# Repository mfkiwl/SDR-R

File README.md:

# SDR-R
Software Defined Radio Receiver(SDR-R) for UMBC Computer Engineering Capstone FA18-SP19

The purpose of this repository will be for tracking of source code changes/additions and team collaboration for the development of this SDR-R. This will facilitate in project organization and documentation.

__Note__: [The home for this repository can be found here](https://github.com/carrera1/SDR-R)

## Directories

__fpga-src/__

Source code for any/all HDL written for the FPGA.

__hw__

Directory for all files related to hardware

__sw-src/__

Source code for any/all C/C++, Matlab/Simulink, or Python code generated.

__vm-info/__

Relevant documentation pertaining to the software development environment is kept here (i.e. list of needed packages). 
This directory also includes an important readme file for setting up important dependencies on your machine. The code 
provided in **sw-src** should function on unix/linux style machines (to include macOS), as long as the relevant dependencies 
are available (mainly pthreads, libftdi, and libusb).

## Set up and Installation

__FPGA__

For any future capstone groups looking back on this, we apologize that the **fpga-src** directory is one of the less organized 
of the bunch. Of the blocks utilized, all but the Xilinx IP cores are here in this repository. These IP cores include a 
clock generator (which should be simple to set up) and a FIFO for interfacing the Rader ("link") block with the FSM 
handling the interfacing with the FTDI chip. The FPGA->FTDI FIFO should have a write width of 16 and a read width of 8. 
The FTDI->FPGA FIFO is written by use for handling the messages sent from the host computer to the FPGA. It is **not** meant 
for interfacing with the Rader block.

__Software__

Instructions for setting up your development environment can be found in **vm-info**. Please, follow the instructions there 
for setting up many of the minor dependencies needed for this project before continuing here.

This project has 2 major dependencies (each with their own sub-dependencies) that are critical for functionality:

* GNU Radio
  - Instructions for setting up found in **vm-info** directory
* libftdi
  - Open source library for writing code the interact with the FT232H bridge we're utilizing
  - Requires **libusb 1.0**, please install this on your system prior to installing libftdi
  - Requires **libconfuse**, please install this on your system prior to installing libftdi

### Installing libftdi

```bash
git://developer.intra2net.com/libftdi
cd libftdi
# READ THE READMEs IN YOUR FAVORITE TEXT EDITOR
```

The libftdi developers included *verbose* instructions within the repository you just cloned. Please read them thoroughly. 
They also include numerous examples demonstrating the functionality of the library, where this project drew heavily from the **stream-test.c**.

The libftdi developers also have their documentation available online which you may find necessary to understand how each 
function works and what their return values may be. [To save you time, you may find it here!](https://www.intra2net.com/en/developer/libftdi/documentation/group__libftdi.html)

Once both GNU Radio and libftdi are installed, software side set up is done. If the FPGA is properly set up, then you're good 
to compile and run the code found in **sw-src**.

## Acknowledgements

This project wouldn't be what it is without the inspiration drawn from the following:
* [This blog post](https://digibird1.wordpress.com/adc-readout-and-usb2-0-data-transfer-with-an-fpga/) for inspiring us to try out an FTDI chip instead of terrible terrible UART.
* [This github repo](https://github.com/RandomReaper/pim-vhdl) for providing an open source FSM for interfacing with the FT232H. Many thanks to [Mssr. Marc Pignat](https://github.com/RandomReaper)!

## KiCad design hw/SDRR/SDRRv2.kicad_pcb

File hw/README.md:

# Hardware Directory

All relevant files or documentation related to hardware should be kept here.

Please keep arrangement neat and logical for the sake of other people's sanity

When convenient or necessary, document this readme to explain the organization of this subdirectory

See other readmes as an example for consistant formatting

## Directories

__SDRR__

KiCad design files

__Chips__

Downloaded library files for IC's in schematic

__Datasheets__

Data sheets for the IC's

__FAB__

Output files from PCB design, for fabrication

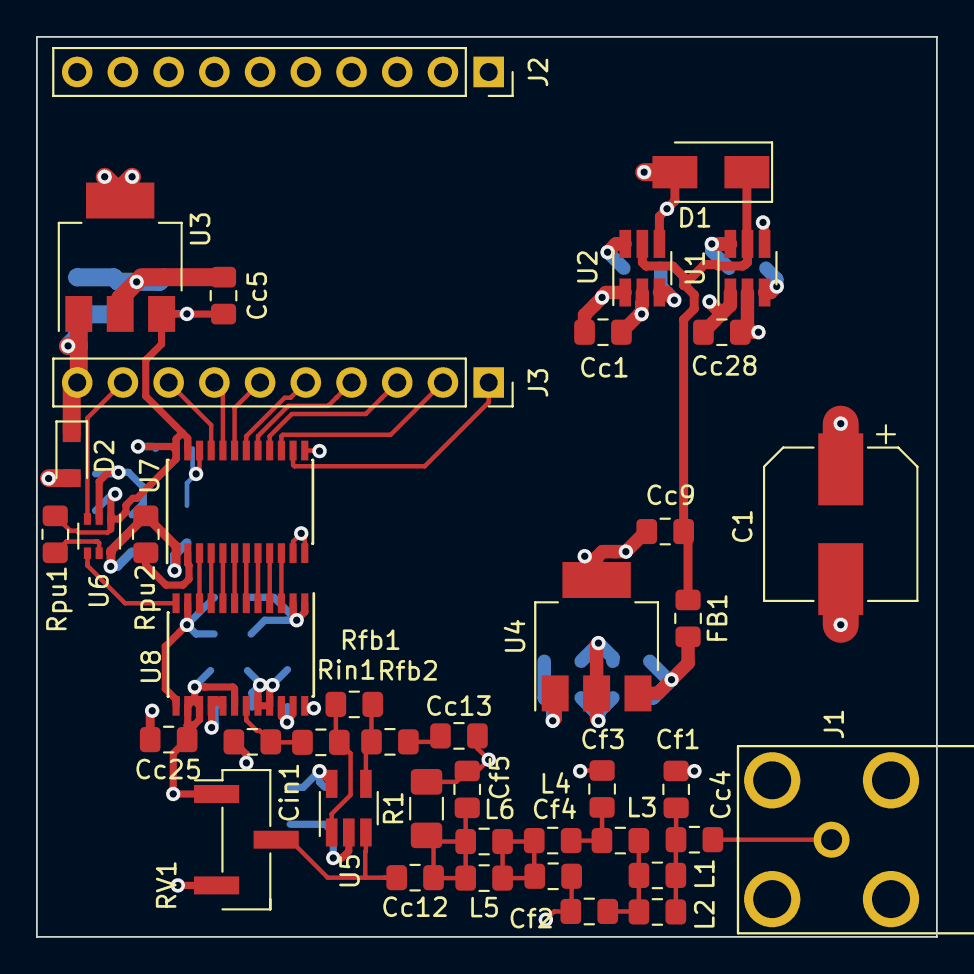
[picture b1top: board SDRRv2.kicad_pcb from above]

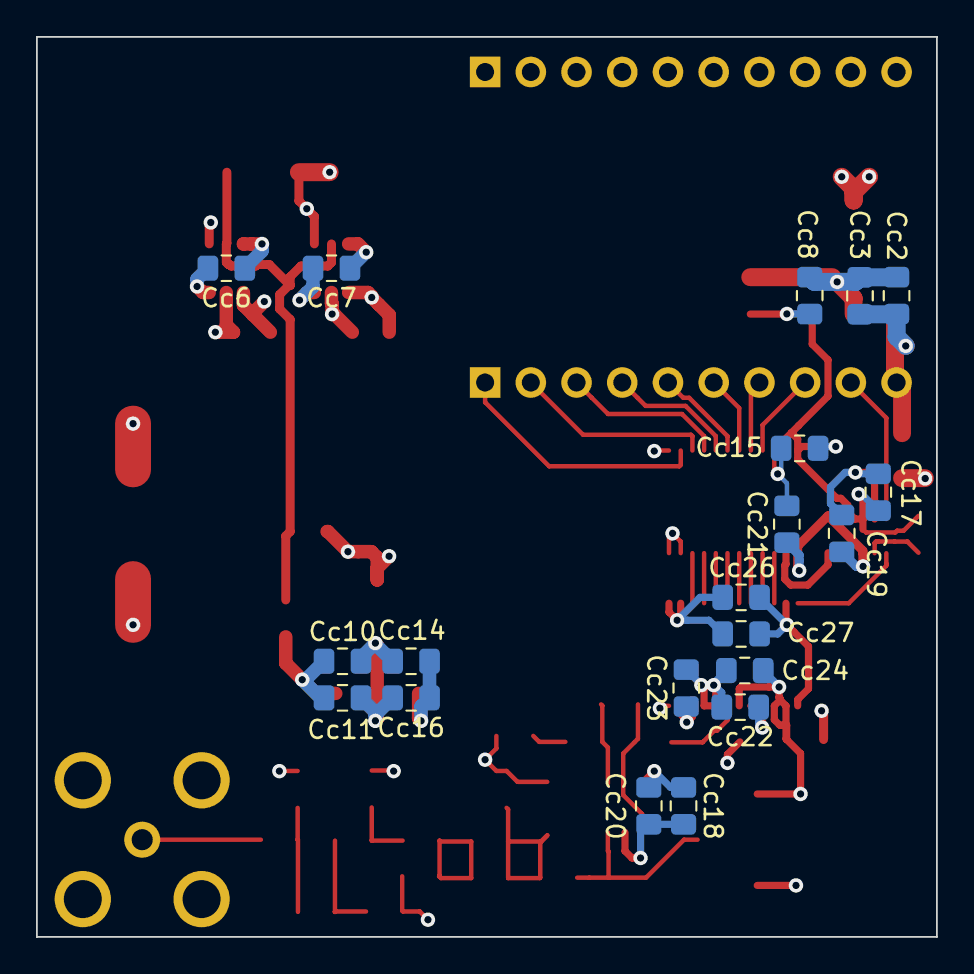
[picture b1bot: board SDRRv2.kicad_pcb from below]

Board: 4 copper layers, 50.0 x 50.0 mm, 62 parts (20 on the bottom side), 43 nets.

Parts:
C1: 47u; CP_Elec_8x6.2
Cc1, Cc3, Cc4, Cc5, Cc6, Cc7, Cc9, Cc10, Cc12, Cc13, Cc14, Cc15, Cc17, Cc18, Cc19, Cc21, Cc25, Cc27, Cc28: 10u; C_0805_2012Metric_Pad1.15x1.40mm_HandSolder
Cc2, Cc8, Cc11, Cc16, Cc20, Cc24, Cc26: 0.1u; C_0805_2012Metric_Pad1.15x1.40mm_HandSolder
Cc22, Cc23: 10uF; C_0805_2012Metric_Pad1.15x1.40mm_HandSolder
Cf1, Cf5: 150pF; C_0805_2012Metric_Pad1.15x1.40mm_HandSolder
Cf2, Cf4: 680pF; C_0805_2012Metric_Pad1.15x1.40mm_HandSolder
Cf3: 910pF; C_0805_2012Metric_Pad1.15x1.40mm_HandSolder
Cin1: 62pF; C_0805_2012Metric_Pad1.15x1.40mm_HandSolder
D1: B120-E3; D_SMA
D2: D_TVS; D_SOD-323_HandSoldering
FB1: L_Core_Ferrite; L_0805_2012Metric_Pad1.15x1.40mm_HandSolder
J1: Conn_Coaxial; TE_5-1634513-1
J2, J3: Conn_01x10_Female; PinSocket_1x10_P2.54mm_Vertical
L1, L2, L3, L4, L5, L6: 2.2u; L_0805_2012Metric_Pad1.15x1.40mm_HandSolder
R1: 50; R_1206_3216Metric_Pad1.42x1.75mm_HandSolder
RV1: R_POT; PinHeader_1x03_P2.54mm_Vertical_SMD_Pin1Left
Rfb1, Rfb2: 270; R_0805_2012Metric_Pad1.15x1.40mm_HandSolder
Rin1: 110; R_0805_2012Metric_Pad1.15x1.40mm_HandSolder
Rpu1, Rpu2: 10k; R_0805_2012Metric_Pad1.15x1.40mm_HandSolder
U1, U2: LM2766M6X_NOPB; SOT-23-6_Handsoldering
U3: UA78M33CDCY; SOT-223-3_TabPin2
U4: UA78M05IDCY; SOT-223-3_TabPin2
U5: OPA354AIDBVR; SOT-23-5_HandSoldering
U6: SN74LVC1T45DCK; SOT-363_SC-70-6
U7: SN74LVC8T245PWR; TSSOP-24_4.4x7.8mm_P0.65mm
U8: ADC1173; TSSOP-24_4.4x7.8mm_P0.65mm

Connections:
+3V3: Cc5.1, Cc8.1, Cc15.2, Cc17.1, Rpu1.1, U3.3, U6.1, U7.23, U7.24
+5V: C1.1, Cc1.1, Cc2.1, Cc3.1, Cc19.1, Cc21.1, Cc26.1, Cc27.1, Cc28.1, D1.2, D2.1, J3.10, Rpu2.1, U1.1, U1.4, U2.1, U2.4, U3.1, U6.6, U7.1, U8.11, U8.13
+5VA: Cc14.1, Cc16.1, Cc18.1, Cc20.1, Cc24.2, Cc25.2, RV1.1, U4.1, U5.5, U8.14, U8.15, U8.18
GNDREF: C1.2, Cc1.2, Cc2.2, Cc3.2, Cc5.2, Cc8.2, Cc9.2, Cc10.2, Cc11.2, Cc13.2, Cc14.2, Cc15.1, Cc16.2, Cc17.2, Cc18.2, Cc19.2, Cc20.2, Cc21.2, Cc22.2, Cc23.2, Cc24.1, Cc25.1, Cc26.2, Cc27.2, Cc28.2, Cf1.2, Cf2.2, Cf3.2, Cf4.2, Cf5.2, Cin1.2, D2.2, J1.2, J2.10, R1.2, RV1.3, U1.2, U2.2, U3.2, U4.2, U5.2, U6.2, U7.11, U7.12, U7.13, U7.22, U8.1, U8.2, U8.20, U8.21, U8.24
unnamed: Cc4.1, J1.1
unnamed: Cc4.2, Cf1.1, L1.1, L2.1
unnamed: Cc6.1, U1.6
unnamed: Cc6.2, U1.3
unnamed: Cc7.1, U2.6
unnamed: Cc7.2, U2.3
unnamed: Cc9.1, D1.1, FB1.1, U1.5, U2.5
unnamed: Cc10.1, Cc11.1, FB1.2, U4.3
unnamed: Cc12.1, Cf5.1, L5.2, L6.2, R1.1
unnamed: Cc12.2, RV1.2, U5.3
unnamed: Cc13.1, Rfb2.2
unnamed: Cc22.1, U8.16, U8.17
unnamed: Cc23.1, U8.22, U8.23
unnamed: Cf2.1, L1.2, L2.2, L3.1
unnamed: Cf3.1, L3.2, L4.1
unnamed: Cf4.1, L4.2, L5.1, L6.1
unnamed: Cin1.1, Rin1.2, U8.19
unnamed: J3.1, U7.14
unnamed: J3.2, U7.15
unnamed: J3.3, U7.16
unnamed: J3.4, U7.17
unnamed: J3.5, U7.18
unnamed: J3.6, U7.19
unnamed: J3.7, U7.20
unnamed: J3.8, U7.21
unnamed: J3.9, U6.3
unnamed: Rfb1.1, Rin1.1, U5.1
unnamed: Rfb1.2, Rfb2.1, U5.4
unnamed: Rpu1.2, U6.5
unnamed: Rpu2.2, U7.2
unnamed: U6.4, U8.12
unnamed: U7.3, U8.10
unnamed: U7.4, U8.9
unnamed: U7.5, U8.8
unnamed: U7.6, U8.7
unnamed: U7.7, U8.6
unnamed: U7.8, U8.5
unnamed: U7.9, U8.4
unnamed: U7.10, U8.3

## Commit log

2018-11-04 Initial commit. Updated readmes.
2018-11-07 Testing file. Remove later
2018-11-07 removing testfile
2018-11-07 Added set up instructions for VM
2018-11-07 Added recommended package to list
2018-11-07 Proof reading/editing
2018-11-07 Proof reading
2018-11-09 Amended sections that were optional
2018-11-14 Added constraints file for CMOD-A7
2018-11-25 Added directory for files related to hardware
2018-11-25 Added entry for HW directory
2018-11-25 minimal edit
2018-11-25 Silly typo
2018-11-25 PCB design
    Kicad design files
    Additional schematic libraries
    Gerber files as submitted for order
    Data sheets for IC's
    Digikey order PDF
2018-11-26 Copy of Digilent GPIO test which we will modify
    We plan to work off of this initial commit towards our final UART
    implementation
2018-11-26 Isolating original hdl files for references
2018-11-26 File modified from original by P E
    Most important parts of this will be GPIO.vhd and UART_TX_CTRL
2018-11-26 Initial commit of Tcl scripts. Haven't tested.
    Have not tested these Tcl scripts with the files as modified by P E. May
    consider checking to see if the Tcl scripts permit relative paths rather
    than absolute paths for more portability.
    One reason why this may not work is that the Tcl scripts don't execute
    in the path that they are located in, and may cause issues sourcing the
    hdl files and constraints
2018-11-26 Modified to use relative paths
2018-11-26 Updated mux.vhd UART_TX_CTRL.vhd up_down_counter.vhd GPIO.vhd
    Changes required to compile Vivado.
    The uartState was set to LD_BYTE from RST_REG and the Tera Term is still not receiving any transmitted data. Need to debug and test.
2018-11-26 Updated script to utilize all 4 cores
    Previously only used 2 cores because I made it in a VM.
2018-11-26 Updated to directly receive input to FPGA
    Removed up/down counters
    Added 8-bit register
    Constraints updated including pins 1-8, and 48-41
    Now can receive an input signal and send it to a computer via UART TX
2018-11-27 Uploading again from failed save.
    Re-upload from failed save
2018-11-27 Added note for installing USB drivers for the FPGA
    There is a link embedded in the readme now that has a link to where you can download drivers for communicating serially with the FPGA.
2018-11-28 new constraints
    updated constraints
2019-01-31 Initial commit of HDL & Testbenches for USB Block
2019-02-01 Comments to explain parameters needed for ip core
    Added comments to the dummy file that explain the parameters needed to set up the FIFO with Xilinx's FIFO Generator IP Core.
2019-02-16 Add files via upload
    kHertz = 10;
    f = kHertz*1000; %in kHertz
    sampleFreq = 4*f; %in kHz
    sr = 1/sampleFreq;
    t = sr/2:sr:1-sr/2; %we have 1 seconds of samples in time
2019-02-16 Add files via upload
    is same as before but has shortened time to 0.1 seconds
2019-02-27 Added confirmed working (for TX only) top module.
2019-03-01 Updated Constraints file to match PCB. Bad News :(
    Bad News is that the Pins 15 and 16 are analog inputs, manually routed
    the wires to pmod[0] and pmod[1] on the header to compensate for this.
2019-03-01 Updated constraints file to work w/ PCB. NOTE:
    Pins 15/16 are jumpered to Pmod0 and Pmod1, respectively
2019-03-04 Cleaing up master, moved mpey19's files to new directory. Removing files from master branch.
2019-03-04 Cleaned up master branch, all deleted files moved to new branch called 'Morgan's Branch'
2019-03-04 Updated readme to reflect change from UART to FTDI FIFO
2019-03-04 Moved top module to it's own directory in fpga-src/
2019-03-04 Added new FSM file. DO NOT MODIFY. See comment.
2019-03-04 Updated to reflected new jumper cables soldered on PCB
2019-03-04 Added missing files for Effingham
2019-03-04 Updated Top Module, currently uses doublecounter rather than up_down_counter
2019-03-14 Initial commit. gnuradio flowgraph performing quadrature demodulation
2019-03-22 New FSM implemented with two counters connected to an interleaver.
2019-03-22 New FSM connected to ADC data pins, replaced counters.
2019-05-10 Add files via upload
    This is the working VHDL for the SDR to send data to the Computer. Receive is being tested right now.
2019-05-15 Demo_broken_v1
    VHDL code implementing all components as of 5.15.19. Currently not working.
    Need to include the following IP cores:
    -Binary Counter. Ben used this for his clock generator
    -FIFO's for the state machine
    -Clk_wiz for both the 100/400 mhz clock.
2019-05-16 Edit to Paul's work
    All sources are in FPGA src.
2019-05-16 Added source code for SW for Demo. CC
2019-05-16 Added idiot proof shell script for compilation.
2019-05-17 New code for demo sans Rader on FPGA
2019-05-22 Moving FPGA source files into proper directory
2019-05-22 Organizing, placing things where they go.
2019-05-22 Organizing FPGA source files
2019-05-22 Removed from root dir as it existed in fpga-srcs
2019-05-22 Removing duplicate/unnecessary files
2019-05-22 Removing junk files that should be in local branch
2019-05-22 Reorganizing software source code
2019-05-23 Added more documentation notes
2019-05-24 Significant Updates to README.md
    Should effectively serve as a 'user manual'
2019-05-24 Create LICENSE
2020-01-10 Minor changes to satisfy my OCD
